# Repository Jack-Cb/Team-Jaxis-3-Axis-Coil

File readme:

Sample rate Max is 500k Samples/Second but split between 3 channels
Resolution 24 bits
Max Distance "Not sure yet"

The idea is:

Program #1 Signal Generator
Generate 3 seperate wave forms
|xu[n]|+|yu[n]|+|zu[n]| = h[n], where xu[n] = x[n]/(|<x,y,z>|)  0 <= h[n] <= 3

Generate code to vary signals at some expected rate
Vary amplitude, 0 - 2^12. 2^12 bias so, 2^12 represents 0V
Vary frequency, Max signal frequency is 1Khz, 

Generate a copy of the signal but with noise added. This should be the one sent to the DSP and the original should be sent to the analysis
Sample each wave form at a frequency of 500k/3, alternate T_s time between x, y, z to match ADC
Send data through socket to signal processor program to simulate SPI
Send data through socket to analysis program

Program #2 Real SPI management version
Basically just packages SPI values into a vector for the DSP program
Configures the SPI interfaces

Program #3 DSP
Recieve 3 packages of 24 bytes
Filter

Program #4 Transmit Handling,
Recieve information about frequency selection and transmit it to the DSP program

Program #5 Anaylsis
Recieve the original signal, (noisy signal?), and dsp signal.
Perform various analysis to determine the effectiveness of the dsp program

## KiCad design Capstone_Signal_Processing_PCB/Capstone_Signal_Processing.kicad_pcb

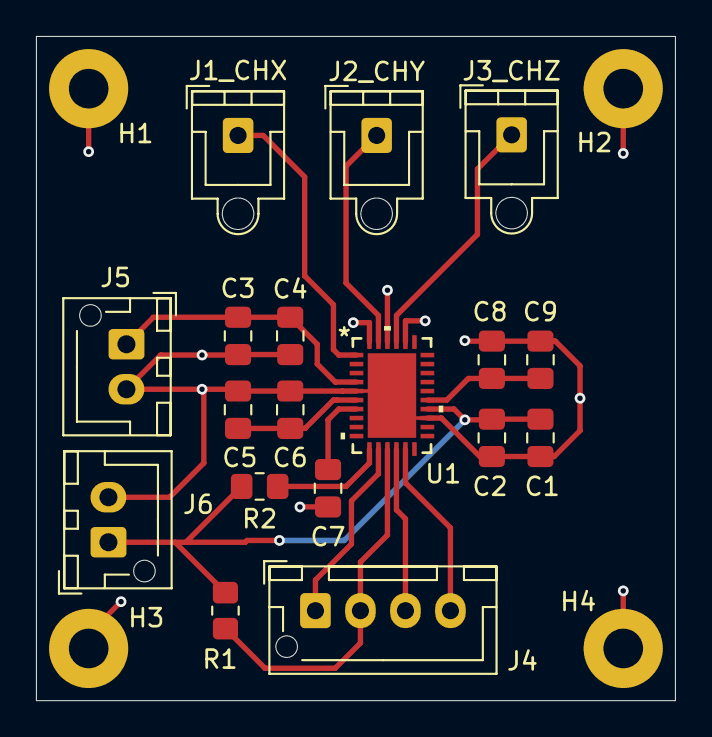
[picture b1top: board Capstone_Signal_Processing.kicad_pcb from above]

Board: 4 copper layers, 35.5 x 36.9 mm, 22 parts (0 on the bottom side), 14 nets.

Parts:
C1, C4, C6, C7, C8: 0.1u; C_0805_2012Metric_Pad1.18x1.45mm_HandSolder
C2, C3, C5, C9: 1u; C_0805_2012Metric_Pad1.18x1.45mm_HandSolder
H1, H2, H3, H4: MountingHole_Pad; MountingHole_2.2mm_M2_Pad
J1_CHX, J2_CHY, J3_CHZ: Conn_01x01; JST_XH_B1B-XH-AM_1x01_P2.50mm_Vertical
J4: Conn_01x04; JST_XH_B4B-XH-AM_1x04_P2.50mm_Vertical
J5, J6: Conn_01x02; JST_XH_B2B-XH-AM_1x02_P2.50mm_Vertical
R1, R2: 1M; R_0805_2012Metric_Pad1.20x1.40mm_HandSolder
U1: AD4170-4BCPZ; CP-32-34_ADI

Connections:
+3.3V: C1.1, C2.1, J6.1, R1.1, R2.2, U1.20 (IOVDD)
+5V: C3.1, C4.1, J5.1, U1.4 (AVDD)
/CH_X: J1_CHX.1, U1.1 (AIN0)
/CH_Y: J2_CHY.1, U1.31 (AIN2)
/CH_Z: J3_CHZ.1, U1.29 (AIN4)
/CS: J4.2, R1.2, U1.13 (*CS)
/SCLK: J4.1, U1.12 (SCLK)
/SDI: J4.4, U1.15 (SDI)
/SDO: J4.3, U1.14 (SDO)
GND: C1.2, C2.2, C3.2, C4.2, C5.1, C6.1, C7.1, C8.2, C9.2, H1.1, H2.1, H3.1, H4.1, J5.2, J6.2, U1.5 (AVSS), U1.19 (DGND), U1.28 (AIN5), U1.30 (AIN3), U1.32 (AIN1), U1.33 (EPAD)
unnamed: R2.1, U1.11 (*SYNC_IN)
unnamed: C7.2, U1.7 (REFOUT)
unnamed: C5.2, C6.2, U1.6 (REGCAP_A)
unnamed: C8.1, C9.1, U1.21 (REGCAP_D)

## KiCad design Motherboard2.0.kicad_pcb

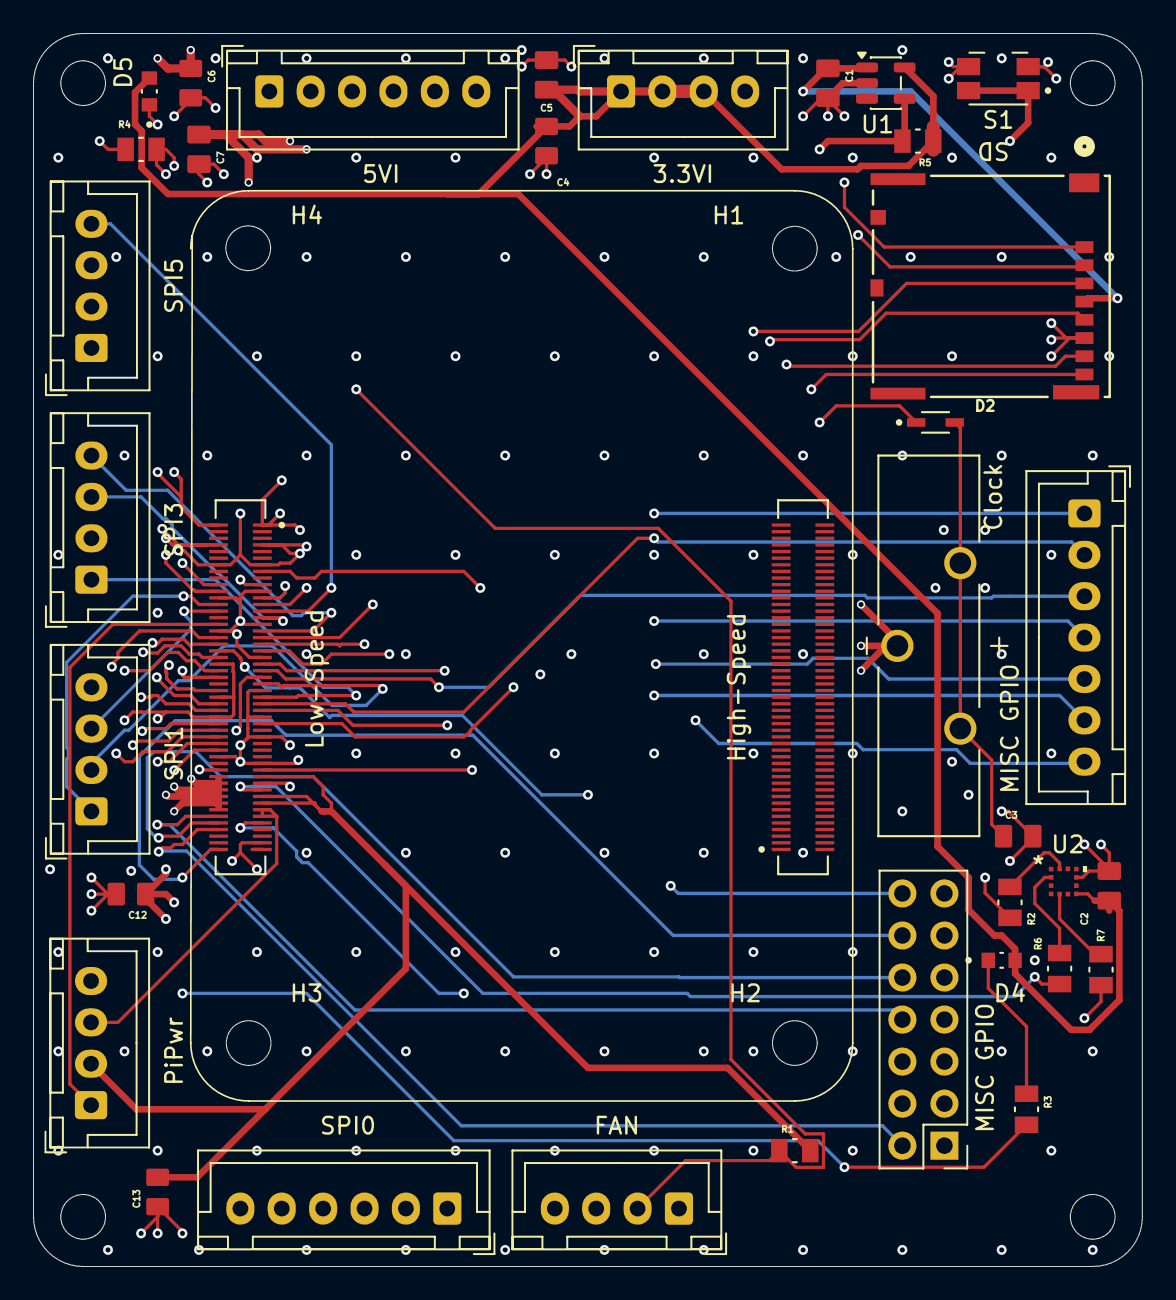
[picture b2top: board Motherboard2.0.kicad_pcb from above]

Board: 6 copper layers, 67.0 x 74.5 mm, 44 parts (0 on the bottom side), 57 nets.

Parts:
3.3VI: Conn_01x04_Socket; JST_XH_B4B-XH-A_1x04_P2.50mm_Vertical
5VI: Conn_01x06_Socket; JST_XH_B6B-XH-A_1x06_P2.50mm_Vertical
C1: 10u; CAPC2012X140N
C2: 4.7u; CAPC2012X140N
C3: 1uF; CAPC2012X135N
C4, C6, C12, C13: 0.1uF; CAPC2012X95N
C5, C7: 10uF; CAPC2012X140N
Clock: 1074; BAT_1074
D2: ZMV829BTA; SOD2512X116N
D4, D5: LTST-C190KRKT; LEDC1608X35N
FAN: Conn_01x04_Socket; JST_XH_B4B-XH-A_1x04_P2.50mm_Vertical
H1, H2, H3, H4, H5, H6, H7, H8: MountingHole; MountingHole_2.7mm_M2.5
High-Speed: 10164227-1001A1RLF; AMPHENOL_10164227-1001A1RLF
Low-Speed: 10164227-1001A1RLF; AMPHENOL_10164227-1001A1RLF
MISC GPIO: Conn_02x07_Odd_Even; PinHeader_2x07_P2.54mm_Vertical
MISC GPIO#2: Conn_01x07_Socket; JST_XH_B7B-XH-A_1x07_P2.50mm_Vertical
PiPwr: Conn_01x04_Socket; JST_XH_B4B-XH-A_1x04_P2.50mm_Vertical
R1, R5: 10k; RESC2012X65N
R2, R6, R7: 2.7k; RESC2012X65N
R3, R4: 1k; RESC2012X65N
S1: EVQ-P7A01P; SW_EVQ-P7A01P
SD: 5033981892; CONN_503398-1892_MOL
SPI0: Conn_01x06_Socket; JST_XH_B6B-XH-A_1x06_P2.50mm_Vertical
SPI1, SPI3, SPI5: Conn_01x04_Socket; JST_XH_B4B-XH-A_1x04_P2.50mm_Vertical
U1: RT9742GGJ5; SOT-23-5
U2: MXC6655XA; MXC6655XA_MEM

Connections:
1.8VO: Low-Speed.87, Low-Speed.89, PiPwr.3
3.3VI: 3.3VI.1, 3.3VI.2, 3.3VI.3, C2.1, C4.1, C5.1, D4.A, D5.A, R5.1, U1.5 (IN), U2.7 (VDD)
3.3VO: C13.2, Low-Speed.77, Low-Speed.83, Low-Speed.85, PiPwr.2, R1.2
5VI: 5VI.1, 5VI.2, 5VI.3, 5VI.4, C6.1, C7.1, C12.1, Low-Speed.78, Low-Speed.80, Low-Speed.82, Low-Speed.84, Low-Speed.86, Low-Speed.88
BT_nDisable: Low-Speed.92, MISC GPIO.10
EEPROM_nWP: Low-Speed.19, MISC GPIO.4
FANPWM: FAN.2, Low-Speed.20, R1.1
GND: 3.3VI.4, 5VI.5, 5VI.6, C1.2, C2.2, C3.2, C4.2, C5.2, C6.2, C7.2, C12.2, C13.1, Clock.N, FAN.3, Low-Speed.1, Low-Speed.2, Low-Speed.7, Low-Speed.8, Low-Speed.13, Low-Speed.14, Low-Speed.21, Low-Speed.24, Low-Speed.31, Low-Speed.34, Low-Speed.41, Low-Speed.44, Low-Speed.51, Low-Speed.54, Low-Speed.59, Low-Speed.60, Low-Speed.65, Low-Speed.66, Low-Speed.72, Low-Speed.73, Low-Speed.97, MISC GPIO.1, MISC GPIO.3, MISC GPIO.5, MISC GPIO.7, MISC GPIO.9, MISC GPIO.11, MISC GPIO.13, PiPwr.4, R4.2, S1.2_1, S1.2_2, SD.6 (VSS), U1.2 (GND), U2.9 (GND)
GPIO0: Low-Speed.35, SPI0.5
GPIO1: Low-Speed.36, SPI0.4
GPIO2: Low-Speed.57, MISC GPIO#2.1
GPIO3: Low-Speed.55, MISC GPIO#2.2
GPIO4: Low-Speed.53, SPI3.1
GPIO5: Low-Speed.33, SPI3.4
GPIO6: Low-Speed.29, SPI3.3
GPIO7: Low-Speed.38, SPI3.2
GPIO8: Low-Speed.40, SPI0.1
GPIO9: Low-Speed.39, SPI0.3
GPIO10: Low-Speed.43, SPI0.2
GPIO11: Low-Speed.37, SPI0.6
GPIO12: Low-Speed.32, PiPwr.1
GPIO13: Low-Speed.27, SPI5.4
GPIO14: Low-Speed.56, SPI5.3
GPIO15: Low-Speed.52, SPI5.1
GPIO17: Low-Speed.49, SPI1.2
GPIO19: Low-Speed.25, SPI1.4
GPIO20: Low-Speed.28, SPI1.3
GPIO21: Low-Speed.26, SPI1.1
GPIO22: Low-Speed.45, MISC GPIO#2.3, R7.1
GPIO23: Low-Speed.48, MISC GPIO#2.7
GPIO24: Low-Speed.46, MISC GPIO#2.6
GPIO25: Low-Speed.42, MISC GPIO#2.5
GPIO26: Low-Speed.23, SPI5.2
GPIO27: Low-Speed.47, MISC GPIO#2.4
LED_nACT: Low-Speed.22, R3.2
unnamed: C3.1, Clock.P_1, Clock.P_2, D2.A
unnamed: D4.C, R3.1
unnamed: D5.C, R4.1
unnamed: R7.2, U2.5 (INT)
unnamed: R2.1, U2.12 (SCL)
unnamed: R6.2, U2.2 (SDA)
PMIC_ENABLE: Low-Speed.100, MISC GPIO.12
PWR_BUT: Low-Speed.91, MISC GPIO.14, S1.1_1, S1.1_2
SCL0: Low-Speed.79, R2.2
SDA0: Low-Speed.81, R6.1
SD_CLK: Low-Speed.58, SD.5 (CLK)
SD_CMD: Low-Speed.61, SD.3 (CMD)
SD_DAT0: Low-Speed.64, SD.7 (DA0)
SD_DAT1: Low-Speed.68, SD.8 (DAT1)
SD_DAT2: Low-Speed.70, SD.1 (DAT2)
SD_DAT3: Low-Speed.62, SD.2 (CD/DAT3)
SD_PWR: C1.1, SD.4 (VDD), U1.1 (OUT)
SD_PWR_ON: Low-Speed.76, R5.2, U1.4 (EN)
TACHO: FAN.4, Low-Speed.15
VBAT: D2.K, Low-Speed.75
Wifi_nDisable: Low-Speed.90, MISC GPIO.8
nRPIBOOT: Low-Speed.94, MISC GPIO.2

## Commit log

2025-11-12 Added Coil Array PCB
2025-11-13 Add files via upload
    2-Layer board was the worst decision of my life, but sunk cost fallacy got me. Too close to the deadline. Just a prototype though, will switch to a more improved design 4-layer asap
2026-01-20 Code Start
2026-02-22 Fixes to Signal Processing PCB, Tx-Rx Added
2026-02-26 Final Changes to ADC PCB
2026-03-09 Code Fixes to ADC, Basic Read Working
2026-03-25 Test code fixes
2026-04-01 Add JackFraley PowerConditioningBlock subproject
2026-04-01 Correct README project scope and component naming
2026-04-01 Rename project folder to Jack Fraley- Power Block
2026-04-01 Add PowerBlock component part names to README
2026-04-01 Normalize part list format in README
2026-04-01 Add Jack Fraley Three-Axis-Coil-Sensor project subfolder
2026-04-01 Update JackFraley subfolder README to power conditioning format
2026-04-01 Rework JackFraley README format for CoilArrayBlock
2026-04-01 Refine JackFraley component list format in README
2026-04-01 Add PowerBlock and PowerConditioningBlock images to README
2026-04-01 Add CoilArray PCB image to JackFraley README
2026-04-01 Move PCB image section to bottom of README
2026-04-01 Rotate PowerConditioningBlock image upright
2026-04-10 Update TX/RX Code
2026-04-18 Tx/Rx Fixes Ported to Sigproc Code
2026-04-18 Fixes
2026-05-03 Testing Changes
2026-05-03 TxRx code near finalized, file name fixes
2026-05-03 Website development
2026-05-04 Added camera controls
2026-05-05 initial
2026-05-05 removed old files
2026-05-05 test
2026-05-06 Sigproc code fixes
2026-05-06 Fixes to sigproc
2026-05-12 Fixes to auto init
2026-05-15 Add files via upload
    Changed project name
2026-06-13 File Reordering
